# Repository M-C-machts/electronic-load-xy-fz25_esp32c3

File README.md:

# Electronic Load XY-FZ25 ESP32C3

A custom PCB and firmware add-on for the **XY-FZ25** electronic load, replacing the built-in measurement front-end with a more accurate solution based on the **Seeed XIAO ESP32C3** and an **INA228** high-precision power monitor.

## Overview

The XY-FZ25 is a low-cost programmable DC electronic load. This project adds a small companion board that sits alongside it and provides independent, higher-accuracy measurements of voltage, current, and power, plus a small OLED display and a self-contained LiFePO4 battery so the measurement circuit is fully isolated from the load's power rails.

### Key features

- **INA228** — 20-bit delta-sigma ADC for bus voltage, current, power, and die temperature
- **SH1106 128×64 OLED** — live display of current (mA), bus voltage (V), and die temperature (°C)
- **LiFePO4 cell** — galvanically isolated measurement supply; charged via the XIAO's USB-C port
- **Seeed XIAO ESP32C3** — compact, USB-C, Wi-Fi/BLE capable (Wi-Fi/BLE not used yet)
- Serial debug output at 115200 baud

## Repository structure

```
electronic-load-xy-fz25_esp32c3/
├── hardware/          # KiCad 7 project (schematic + PCB)
│   ├── *.kicad_pro
│   ├── *.kicad_sch
│   └── *.kicad_pcb
└── software/          # PlatformIO firmware (Arduino / ESP-IDF)
    ├── platformio.ini
    └── src/
        └── main.cpp
```

## Hardware

| Component | Description |
|-----------|-------------|
| Seeed XIAO ESP32C3 | MCU, USB-C charging, I²C host |
| INA228 | 20-bit power monitor, I²C addr `0x40` |
| SH1106 OLED 128×64 | I²C display, addr `0x3C` (or `0x3D`) |
| LiFePO4 cell | ~3.2 V nominal, ~3.6 V full |

The KiCad project is located in [`hardware/`](hardware/).

## Software

### Prerequisites

- [PlatformIO](https://platformio.org/) (VS Code extension or CLI)
- Board: **Seeed XIAO ESP32C3** (installed automatically by PlatformIO)

### Dependencies (installed automatically)

```
adafruit/Adafruit GFX Library
adafruit/Adafruit SH110X
adafruit/Adafruit INA228 Library
```

### Build & flash

```bash
# Build only
pio run

# Build and upload (USB-C)
pio run --target upload

# Open serial monitor at 115200 baud
pio device monitor
```

### Configuration

Edit the constants near the top of [`software/src/main.cpp`](software/src/main.cpp):

| Constant | Default | Purpose |
|----------|---------|---------|
| `OLED_ADDR` | `0x3C` | OLED I²C address |
| `INA_ADDR` | `0x40` | INA228 I²C address |
| `DISPLAY_UPDATE_MS` | `500` | Display refresh interval |
| Shunt resistor | `0.015 Ω` | Passed to `ina228.setShunt()` — **must match your actual shunt** |

The INA228 is configured for 256-sample averaging and 1052 µs conversion times for low-noise readings. Adjust `setAveragingCount()` and `setVoltageConversionTime()` / `setCurrentConversionTime()` in `setup()` to trade off noise vs. update rate.

## Serial output

When connected via USB, the firmware prints one line per refresh interval:

```
I=123.456 mA  Vbus=3.3012 V  Tdie=28.50 C
```

## License

MIT

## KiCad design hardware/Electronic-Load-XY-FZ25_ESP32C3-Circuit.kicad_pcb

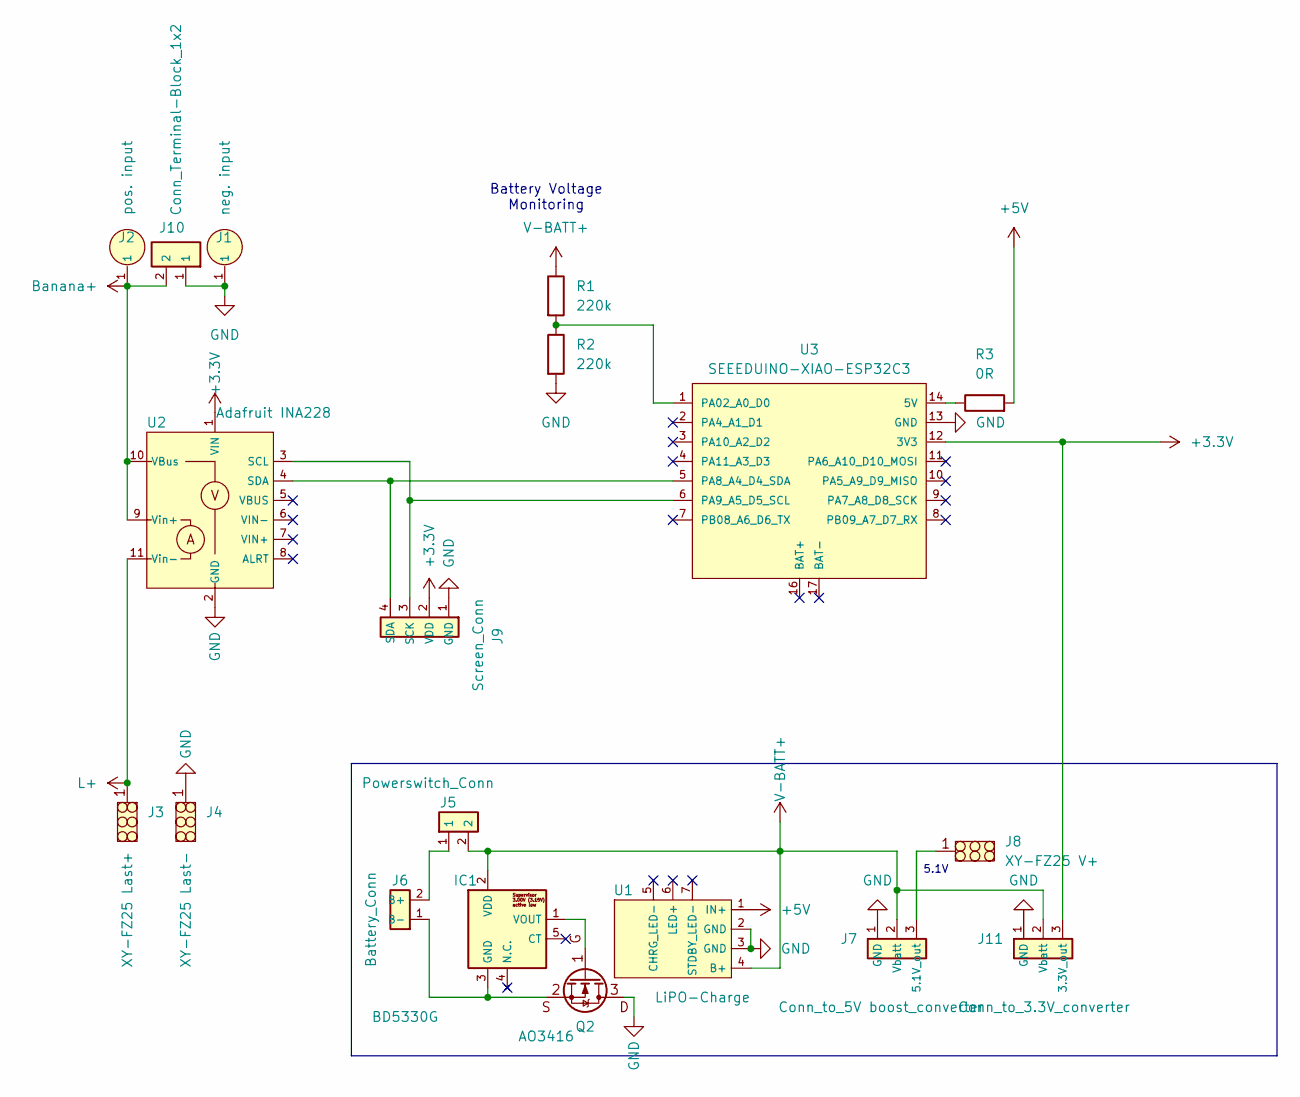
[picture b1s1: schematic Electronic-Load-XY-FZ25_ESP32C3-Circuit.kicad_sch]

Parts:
IC1: BD5330G; SOT95P280X125-5M; Mouser Part Number 755-BD5330G-2MTR
J1, J2: Banana-Socket; banana-socket; Mouser Part Number 534-575-4
J3, J4: mech.-solder-pad_large; Mechc.-solder-pad-large
J5, J6: Conn_1x2_PH; Mechc.-solder-pad_1x2
J7, J11: Conn_1x3_PH; Mechc.-solder-pad_1x3
J8: mech.-solder-pad; Mechc.-solder-pad
J9: Conn_1x4_PH; Conn_1x4_PH_drill dot
J10: Conn_Terminal-Block_1x2
Q2: AO3416; SOT-23
R1, R2: 220k; R_0805_2012Metric
R3: 0R; R_1206_3216Metric_Pad1.30x1.75mm_HandSolder
U1: LiPO-Charge; TP5000-Charge-IC_smal-led
U2: Adafruit INA228; INA228-Footprint
U3: SEEEDUINO-XIAO-ESP32C3

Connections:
+3.3V: J9.2 (VDD), J11.3 (3.3V_out), U2.1 (VIN), U3.12 (3V3)
+5V: R3.2, U1.1 (IN+)
Banana+: J2.1, J10.2, U2.9 (Vin+), U2.10 (VBus)
GND: J1.1, J4.1, J7.1 (GND), J9.1 (GND), J10.1, J11.1 (GND), Q2.3 (D), R2.2, U1.2 (GND), U1.3 (GND), U2.2 (GND), U3.13 (GND)
L+: J3.1, U2.11 (Vin-)
unnamed: IC1.3 (GND), J6.1 (B-), Q2.2 (S)
unnamed: IC1.1 (VOUT), Q2.1 (G)
unnamed: J5.1, J6.2 (B+)
unnamed: J7.3 (5.1V_out), J8.1
unnamed: J9.3 (SCK), U2.3 (SCL), U3.6 (PA9_A5_D5_SCL)
unnamed: J9.4 (SDA), U2.4 (SDA), U3.5 (PA8_A4_D4_SDA)
unnamed: R3.1, U3.14 (5V)
unnamed: R1.2, R2.1, U3.1 (PA02_A0_D0)
V-BATT+: IC1.2 (VDD), J5.2, J7.2 (Vbatt), J11.2 (Vbatt), R1.1, U1.4 (B+)

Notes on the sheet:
Battery Voltage Monitoring
5.1V

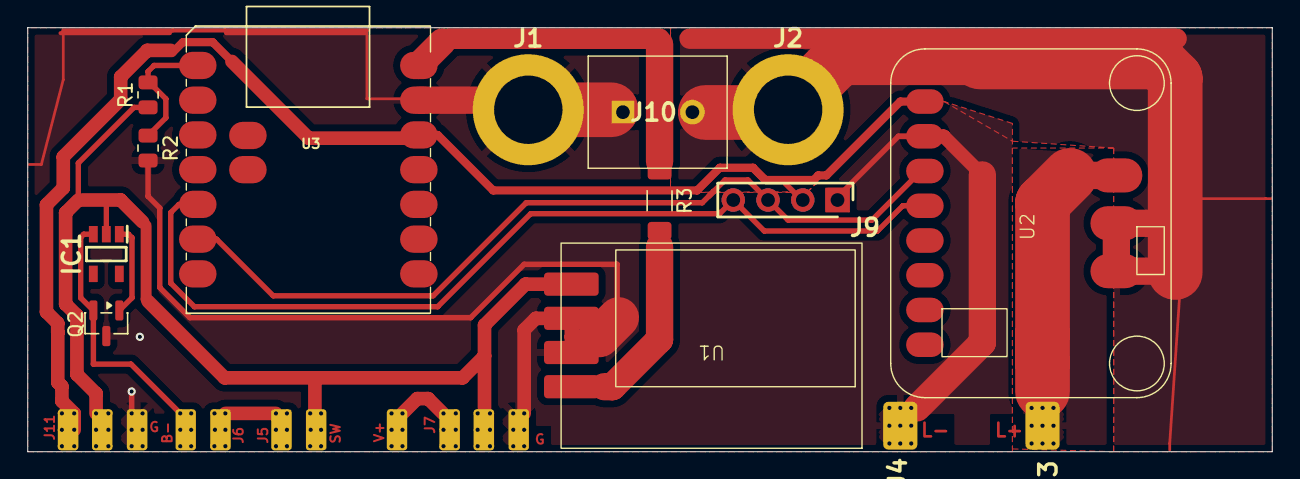
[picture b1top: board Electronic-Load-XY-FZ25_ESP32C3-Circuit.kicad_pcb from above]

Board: 2 copper layers, 91.0 x 31.0 mm, 19 parts (0 on the bottom side), 14 nets.

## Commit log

2026-01-27 Update Folder structure
2026-01-27 Add first working firmware
2026-02-05 Save
2026-02-19 Split electronic-load-xy-fz25_esp32c3 into own repo
